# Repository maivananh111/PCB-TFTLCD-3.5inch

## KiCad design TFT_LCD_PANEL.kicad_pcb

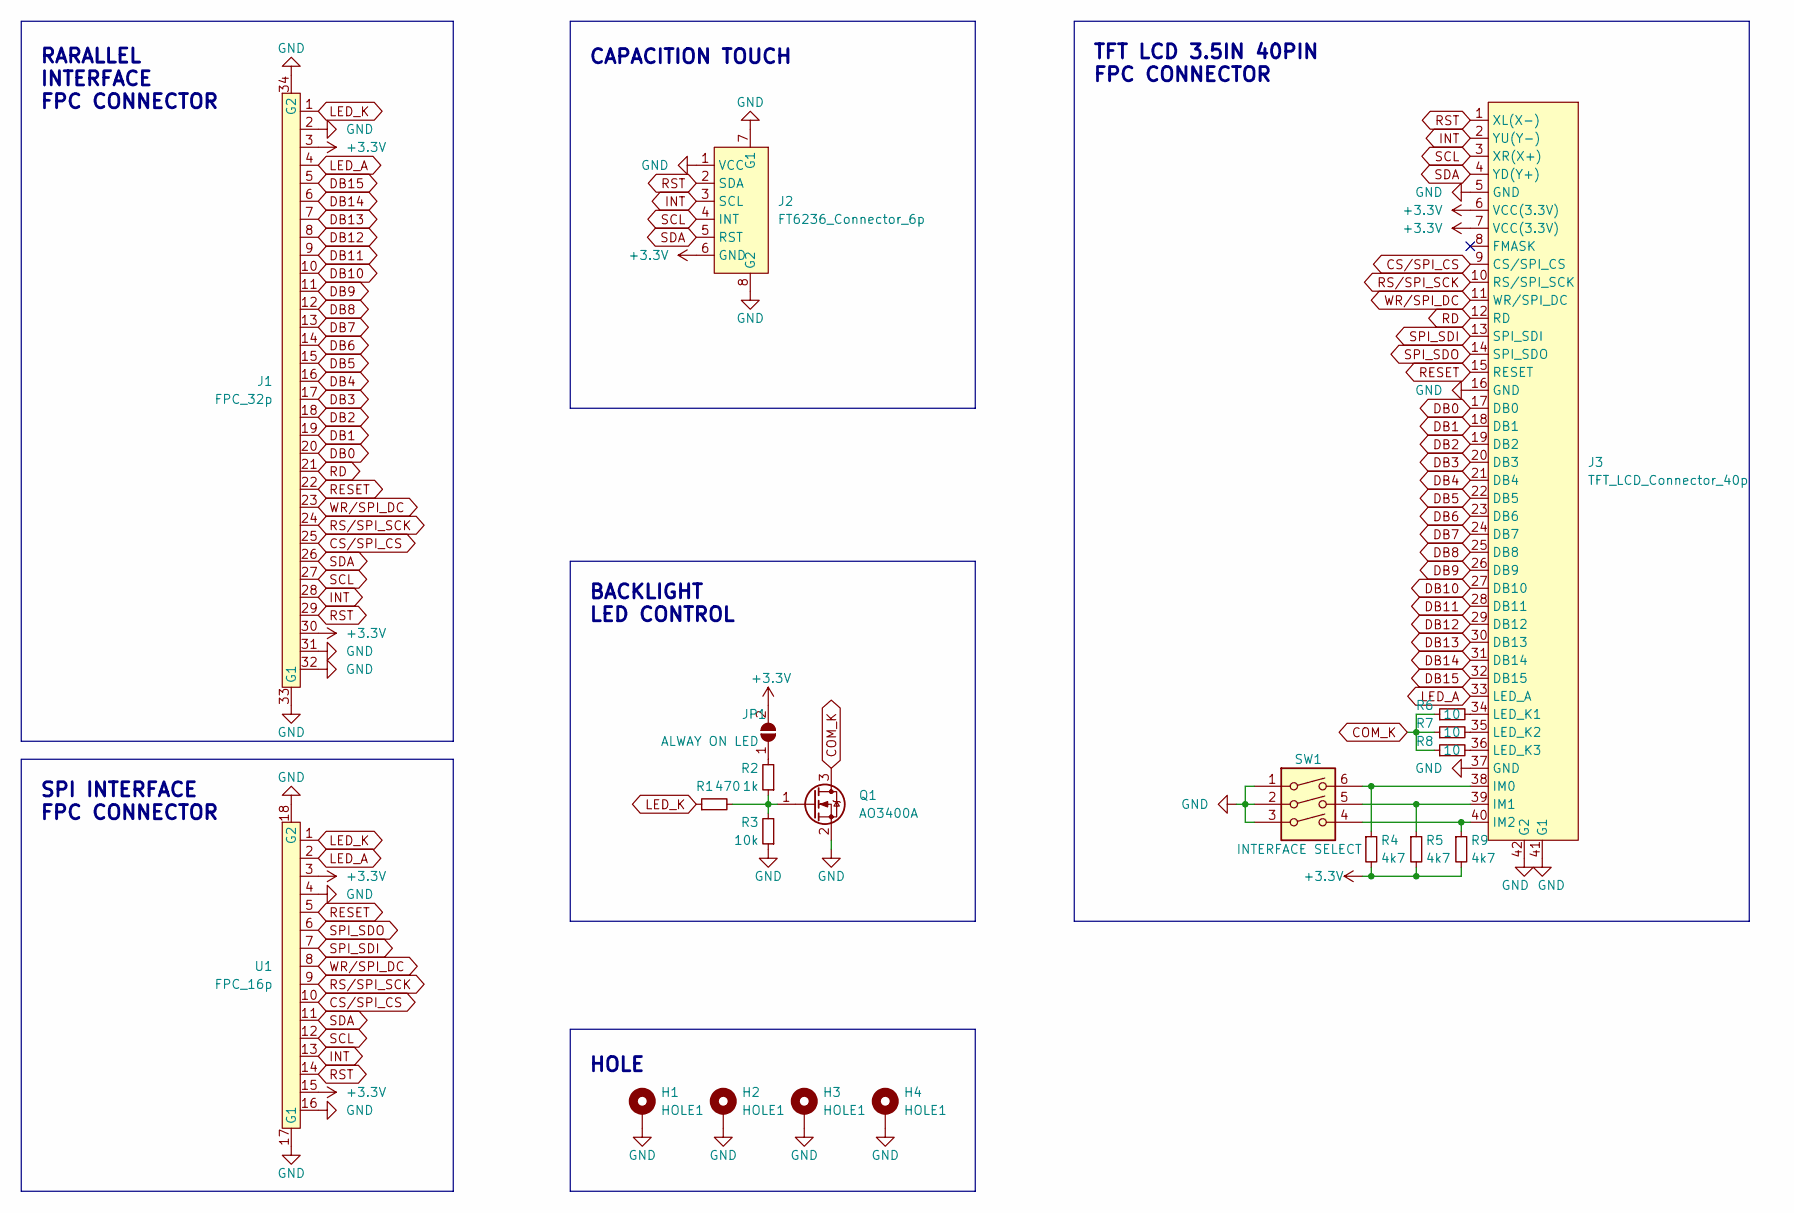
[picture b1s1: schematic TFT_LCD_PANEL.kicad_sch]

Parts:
H1, H2, H3, H4: HOLE1; MountingHole_3.2mm_M3_Pad_Via
J1: FPC_32p
J2: FT6236_Connector_6p; FPC_6p
J3: TFT_LCD_Connector_40p; FPC_40p
JP1: ALWAY ON LED; SolderJumper-2_P1.3mm_Open_RoundedPad1.0x1.5mm
Q1: AO3400A; SOT-23
R1: 470; R_0603_1608Metric
R2: 1k; R_0603_1608Metric
R3: 10k; R_0603_1608Metric
R4, R5, R9: 4k7; R_0603_1608Metric
R6, R7, R8: 10; R_0805_2012Metric
SW1: INTERFACE SELECT; SW_DIP_SPSTx03_Slide_KingTek_DSHP03TS_W7.62mm_P1.27mm
U1: FPC_16p

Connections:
+3.3V: J1.3, J1.30, J2.6 (GND), J3.6 (VCC(3.3V)), J3.7 (VCC(3.3V)), JP1.2 (B), R4.2, R5.2, R9.2, U1.3, U1.15
COM_K: Q1.3 (D), R6.1, R7.1, R8.1
CS/SPI_CS: J1.25, J3.9 (CS/SPI_CS), U1.10
DB0: J1.20, J3.17 (DB0)
DB1: J1.19, J3.18 (DB1)
DB2: J1.18, J3.19 (DB2)
DB3: J1.17, J3.20 (DB3)
DB4: J1.16, J3.21 (DB4)
DB5: J1.15, J3.22 (DB5)
DB6: J1.14, J3.23 (DB6)
DB7: J1.13, J3.24 (DB7)
DB8: J1.12, J3.25 (DB8)
DB9: J1.11, J3.26 (DB9)
DB10: J1.10, J3.27 (DB10)
DB11: J1.9, J3.28 (DB11)
DB12: J1.8, J3.29 (DB12)
DB13: J1.7, J3.30 (DB13)
DB14: J1.6, J3.31 (DB14)
DB15: J1.5, J3.32 (DB15)
GND: H1.1, H2.1, H3.1, H4.1, J1.2, J1.31, J1.32, J1.33 (G1), J1.34 (G2), J2.1 (VCC), J2.7 (G1), J2.8 (G2), J3.5 (GND), J3.16 (GND), J3.37 (GND), J3.41 (G1), J3.42 (G2), Q1.2 (S), R3.1, SW1.1, SW1.2, SW1.3, U1.4, U1.16, U1.17 (G1), U1.18 (G2)
INT: J1.28, J2.3 (SCL), J3.2 (YU(Y-)), U1.13
LED_A: J1.4, J3.33 (LED_A), U1.2
LED_K: J1.1, R1.1, U1.1
unnamed: J3.34 (LED_K1), R6.2
unnamed: J3.35 (LED_K2), R7.2
unnamed: J3.36 (LED_K3), R8.2
unnamed: J3.38 (IM0), R4.1, SW1.6
unnamed: J3.39 (IM1), R5.1, SW1.5
unnamed: J3.40 (IM2), R9.1, SW1.4
unnamed: JP1.1 (A), R2.2
unnamed: Q1.1 (G), R1.2, R2.1, R3.2
RD: J1.21, J3.12 (RD)
RESET: J1.22, J3.15 (RESET), U1.5
RST: J1.29, J2.2 (SDA), J3.1 (XL(X-)), U1.14
RS/SPI_SCK: J1.24, J3.10 (RS/SPI_SCK), U1.9
SCL: J1.27, J2.4 (INT), J3.3 (XR(X+)), U1.12
SDA: J1.26, J2.5 (RST), J3.4 (YD(Y+)), U1.11
SPI_SDI: J3.13 (SPI_SDI), U1.7
SPI_SDO: J3.14 (SPI_SDO), U1.6
WR/SPI_DC: J1.23, J3.11 (WR/SPI_DC), U1.8

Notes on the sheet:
BACKLIGHT LED CONTROL
SPI INTERFACE FPC CONNECTOR
CAPACITION TOUCH
HOLE
RARALLEL INTERFACE FPC CONNECTOR
TFT LCD 3.5IN 40PIN FPC CONNECTOR

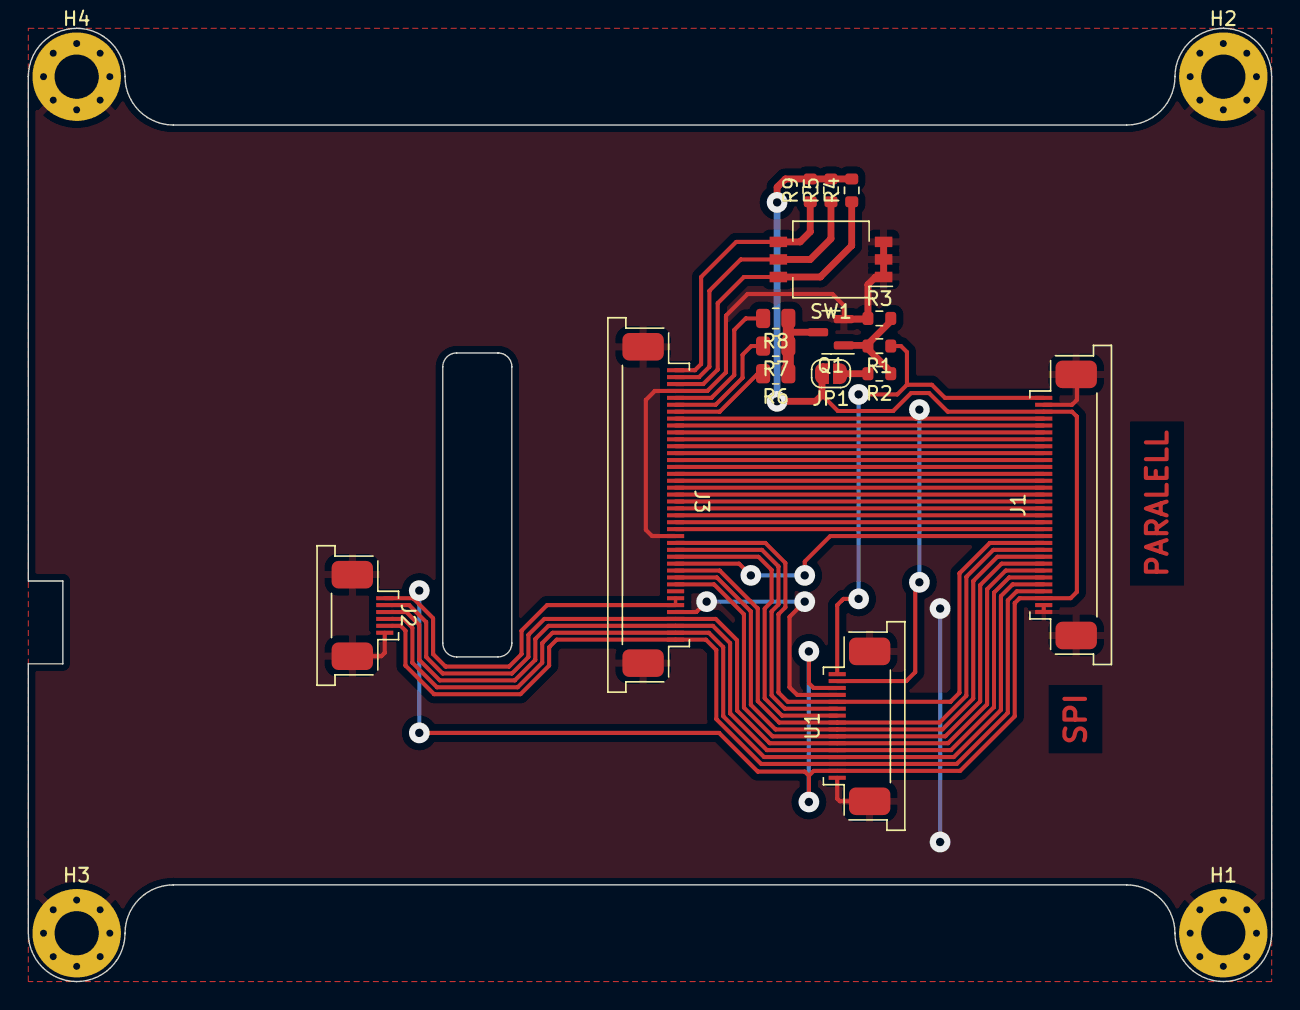
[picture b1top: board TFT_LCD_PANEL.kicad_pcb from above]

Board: 2 copper layers, 90.0 x 69.0 mm, 20 parts (0 on the bottom side), 40 nets.
